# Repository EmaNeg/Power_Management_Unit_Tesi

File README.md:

# Power Management Unit (PMU) per Sistemi Embedded

<div align="center">
  <!-- Sostituisci con i nomi reali dei file immagine esportati -->
  
  &nbsp;&nbsp;&nbsp;&nbsp;&nbsp;&nbsp;&nbsp;&nbsp;&nbsp;&nbsp;&nbsp;&nbsp;&nbsp;&nbsp;&nbsp;&nbsp;&nbsp;&nbsp;
  
</div>

<br>

Questo repository contiene tutti i file di progettazione hardware, le simulazioni e le librerie software per una **Power Management Unit (PMU) integrata**, sviluppata come progetto di Tesi di Laurea Triennale in Ingegneria Elettronica e Tecnologie dell'Informazione presso l'Università degli Studi di Genova.

Il modulo (dimensioni 50x50 mm su PCB a due strati) è progettato per superare il divario tecnologico tra le tensioni variabili delle batterie ai Polimeri di Litio (Li-Po) e le specifiche di alimentazione stabili a 5V richieste dai carichi digitali, garantendo continuità di servizio e sicurezza operativa.

---

## ✨ Caratteristiche Principali (Features)

* **Power Path Management:** Commutazione automatica e trasparente tra sorgente esterna (5V) e batteria, dando priorità all'alimentazione di rete senza azzerare i transitori sul carico.
* **Conversione DC-DC:** Uscita stabile a 5V tramite convertitore Buck-Boost, operante in modo trasparente indipendentemente dallo stato di carica della cella (da 3.0V a 4.2V).
* **Ricarica Li-Po 1S:** Algoritmo CC-CV integrato basato su architettura lineare, con interruzione automatica a 4.2V.
* **Protezione Hardware (BMS):** Modulo di protezione contro sovrascarica (< 2.4V), sovraccarica (> 4.3V) e cortocircuiti.
* **Fuel Gauging I²C:** Stima accurata dello Stato di Carica (SOC) e *alert* hardware tramite algoritmo ModelGauge, senza necessità di resistenze di shunt, azzerando la deriva dell'errore.

---

## 🛠 Architettura Hardware

Il progetto è stato interamente sviluppato utilizzando **KiCad 9.0**. Il sistema si basa sui seguenti circuiti integrati:

| Sottosistema | Modello IC | Produttore | Funzione Principale |
| :--- | :--- | :--- | :--- |
| **DC-DC Converter** | TPS630701 | Texas Instruments | Convertitore Buck-Boost 2.4 MHz fisso a 5V. |
| **Battery Charger** | MCP73831 | Microchip | Controller lineare per ricarica Li-Po 1S (CC-CV). |
| **Fuel Gauge** | MAX17048 | Maxim Integrated | Sensore SOC I²C con algoritmo ModelGauge. |
| **Protection (BMS)** | DW01A + FS8205 | HM Semi / IC Fortune | IC di protezione batteria e doppio MOSFET N-Channel. |
| **Power Path** | DMP1045U-7 | Diodes Inc. | MOSFET P-Channel per commutazione automatica. |

---

## 📊 Prestazioni e Risultati Sperimentali

Il circuito è stato collaudato strumentalmente, registrando ottimi risultati in termini di efficienza energetica e stabilità del segnale:

* **Efficienza Energetica ($\eta$):** Compresa tra il **78.3%** (a pieno carico, ~1.25A) e il **90%** (a carico ridotto, ~100mA).
* **Ripple di Tensione:** Estremamente contenuto, registrando un picco massimo di **60 mV** a 300 mA (90 kHz) e **40 mV** a 1.4 A (390 kHz).
* **Carico Elettrico Massimale:** Il sistema sostiene in sicurezza carichi continui fino a **1.3A a 4.92V** (circa 6.4W in uscita) prima dell'intervento del fusibile resettabile hardware (tarato per sgancio a 1.6A).

<div align="center">
  <!-- Aggiungi nella repo l'immagine dei grafici dell'oscilloscopio se lo desideri -->
  
  &nbsp;&nbsp;&nbsp;&nbsp;&nbsp;&nbsp;
  
</div>

---

## 💻 Libreria Software (Firmware)

A supporto dell'hardware, è stata sviluppata una libreria firmware in **C++** dedicata al sensore MAX17048. 
La libreria permette ai microcontrollori host (es. Arduino, ESP32, STM32) di interfacciarsi facilmente con la PMU per:
- Lettura in tempo reale della tensione della cella ($V_{cell}$) e del SOC (%).
- Monitoraggio del rateo di ricarica/scarica tramite registro `CRATE`.
- Gestione interrupt hardware sul pin `ALRT` per avvisi di sotto-tensione programmabili e sleep mode per il risparmio energetico.

---

## 📁 Struttura della Repository

```text
├── Hardware/
│   ├── Kicad_files/        # File di progetto sorgente (Schematici, Layout PCB)
│   ├── Production/         # File Gerber e Drill pronti per la produzione industriale
│   ├── Assembly/           # File BOM (Bill of Materials) e CPL per assemblaggio SMT Pick & Place
│   └── 3D_Models/          # Rendering 3D della scheda top/bottom (STEP/PNG)
├── Simulations/            # File di simulazione SPICE dei blocchi funzionali (Proteus 8)
├── Firmware/               # Libreria C++ custom per MAX17048 e sketch di test (Arduino)
├── Datasheets/             # PDF dei datasheet originali dei componenti utilizzati
├── Docs/                   # Immagini, grafici di test termici/ripple, schemi e documentazione extra
└── README.md

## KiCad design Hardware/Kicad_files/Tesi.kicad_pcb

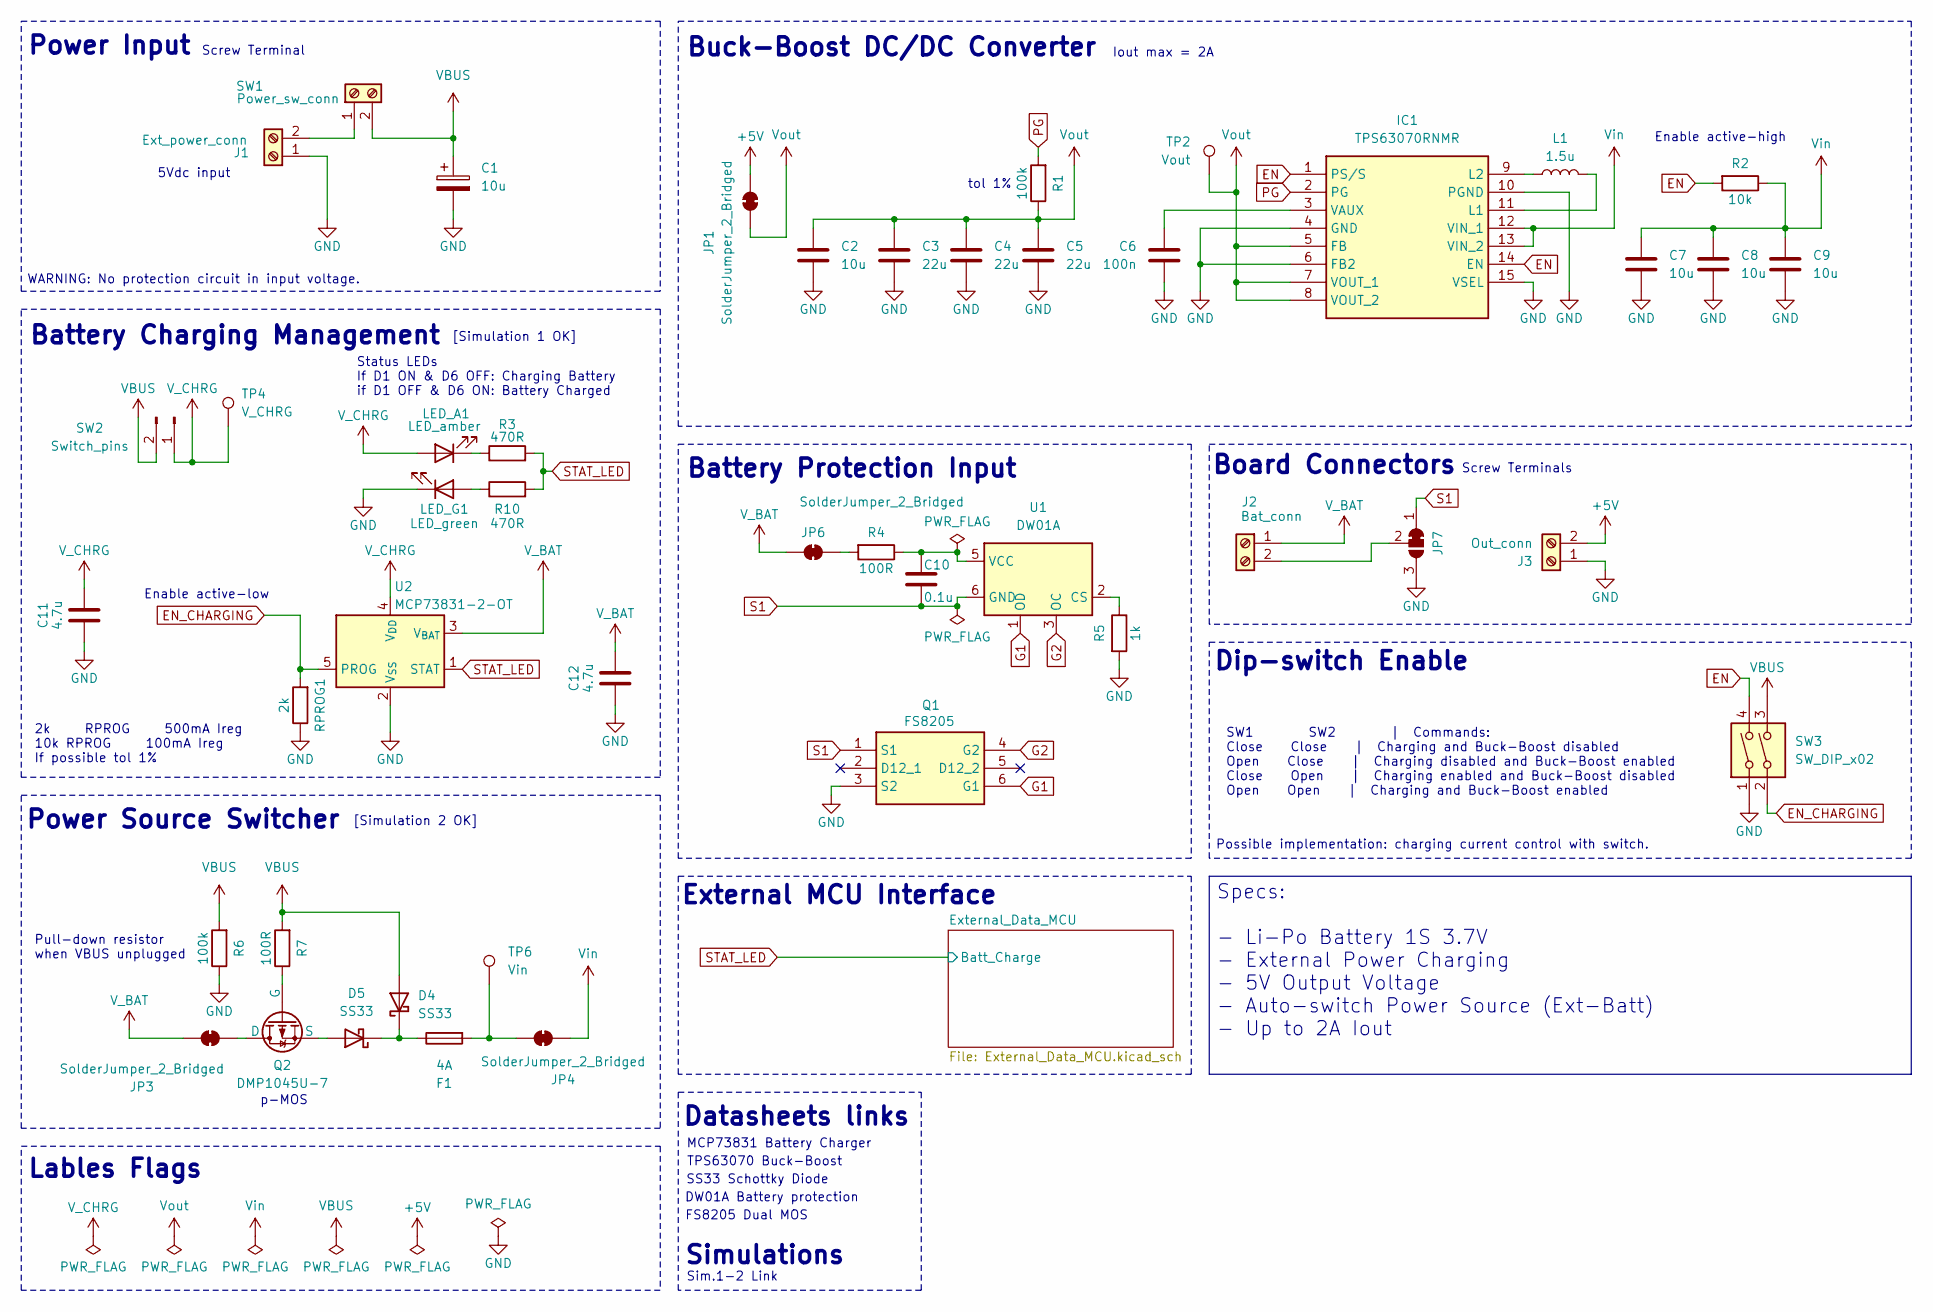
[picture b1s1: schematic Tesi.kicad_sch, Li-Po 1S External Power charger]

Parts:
C1: 10u; CP_EIA-3216-18_Kemet-A
C2, C7: 10u; C_0603_1608Metric
C3, C4, C5: 22u; C_0805_2012Metric
C6: 100n; C_0402_1005Metric
C8, C9: 10u; C_0805_2012Metric
C10: 0.1u; C_0402_1005Metric
C11, C12: 4.7u; C_0603_1608Metric
D4, D5: SS33; D_SMA
F1: 4A; Fuse_1812_4532Metric_Pad1.30x3.40mm_HandSolder
IC1: TPS63070RNMR; TPS630701RNMR; Manufacturer_Part_Number TPS63070RNMR; Mouser Part Number 595-TPS63070RNMR
J1: Ext_power_conn; KF3012P
J2: Bat_conn; KF3012P
J3: Out_conn; KF3012P
JP1, JP3, JP4, JP6: SolderJumper_2_Bridged; SolderJumper-2_P1.3mm_Bridged_RoundedPad1.0x1.5mm
JP7: SolderJumper_3_Bridged12; SolderJumper-3_P1.3mm_Bridged12_RoundedPad1.0x1.5mm_NumberL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
L1: 1.5u; L_Coilcraft_XxL4020
LED_A1: LED_amber; LED_0603_1608Metric
LED_G1: LED_green; LED_0603_1608Metric
Q1: FS8205; Manufacturer_Part_Number FS8205
Q2: DMP1045U-7; SOT-23-GATE
R1: 100k; R_0603_1608Metric
R2: 10k; R_0603_1608Metric
R3, R10: 470R; R_0805_2012Metric
R4, R7: 100R; R_0402_1005Metric
R5: 1k; R_0603_1608Metric
R6: 100k; R_0402_1005Metric
RPROG1: 2k; R_0603_1608Metric
SW1: Power_sw_conn; KF3012P
SW2: Switch_pins; PinHeader_1x02_P2.54mm_Vertical_SMD_Pin1Left
SW3: SW_DIP_x02; SW_DIP_SPSTx02_Slide_KingTek_DSHP02TS_W7.62mm_P1.27mm
TP2: Vout; TestPoint_Pad_D2.0mm
TP4: V_CHRG; TestPoint_Pad_D2.0mm
TP6: Vin; TestPoint_Pad_D2.0mm
U1: DW01A; SOT-23-6
U2: MCP73831-2-OT; SOT-23-5

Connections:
+5V: J3.2, JP1.2 (B)
EN: IC1.1 (PS/S), IC1.14 (EN), R2.2, SW3.4
EN_CHARGING: RPROG1.2, SW3.2, U2.5 (PROG)
G1: Q1.6 (G1), U1.1 (OD)
G2: Q1.4 (G2), U1.3 (OC)
GND: C1.2, C2.2, C3.2, C4.2, C5.2, C6.2, C7.2, C8.2, C9.2, C11.1, C12.1, IC1.4 (GND), IC1.6 (FB2), IC1.10 (PGND), IC1.15 (VSEL), J1.1, J3.1, JP7.3 (B), LED_G1.1 (K), Q1.3 (S2), R5.2, R6.1, RPROG1.1, SW3.1, U2.2 (V_{SS}); also elsewhere on the board
unnamed: D4.1 (K), D5.1 (K), F1.1
unnamed: D5.2 (A), Q2.3 (S)
unnamed: IC1.11 (L1), L1.2
unnamed: IC1.9 (L2), L1.1
unnamed: C6.1, IC1.3 (VAUX)
unnamed: J1.2, SW1.1
unnamed: J2.2, JP7.2 (C)
unnamed: JP3.2 (B), Q2.1 (D)
unnamed: F1.2, JP4.1 (A), TP6.1
unnamed: JP6.2 (B), R4.2
unnamed: LED_A1.1 (K), R3.1
unnamed: LED_G1.2 (A), R10.1
unnamed: Q2.2 (G), R7.1
unnamed: R5.1, U1.2 (CS)
unnamed: C10.2, R4.1, U1.5 (VCC)
PG: IC1.2 (PG), R1.2
S1: C10.1, JP7.1 (A), Q1.1 (S1), U1.6 (GND)
STAT_LED: R3.2, R10.2, U2.1 (STAT); also elsewhere on the board
VBUS: C1.1, D4.2 (A), R6.2, R7.2, SW1.2, SW2.2, SW3.3
V_BAT: C12.2, J2.1, JP3.1 (A), JP6.1 (A), U2.3 (V_{BAT}); also elsewhere on the board
V_CHRG: C11.2, LED_A1.2 (A), SW2.1, TP4.1, U2.4 (V_{DD})
Vin: C7.1, C8.1, C9.1, IC1.12 (VIN_1), IC1.13 (VIN_2), JP4.2 (B), R2.1
Vout: C2.1, C3.1, C4.1, C5.1, IC1.5 (FB), IC1.7 (VOUT_1), IC1.8 (VOUT_2), JP1.1 (A), R1.1, TP2.1

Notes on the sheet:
tol 1%
Power Input
Buck-Boost DC/DC Converter
Lables Flags
Power Source Switcher
Enable active-low
2k RPROG 500mA Ireg 10k RPROG 100mA Ireg If possible tol 1%
Iout max = 2A
Battery Protection Input
[Simulation 2 OK]
Simulations
Enable active-high
MCP73831 Battery Charger
p-MOS
Screw Terminals
External MCU Interface
TPS63070 Buck-Boost
Battery Charging Management
5Vdc input
Datasheets links
FS8205 Dual MOS
[Simulation 1 OK]
DW01A Battery protection
Possible implementation: charging current control with switch.
Board Connectors
SW1 SW2 | Commands: Close Close | Charging and Buck-Boost disabled Open Close | Charging disabled and Buck-Boost enabled Close Open | Charging enabled and Buck-Boost disabled Open Open | Charging and Buck-Boost enabled
SS33 Schottky Diode
WARNING: No protection circuit in input voltage.
Status LEDs If D1 ON & D6 OFF: Charging Battery if D1 OFF & D6 ON: Battery Charged
Dip-switch Enable
Screw Terminal
Pull-down resistor when VBUS unplugged
Sim.1-2 Link
Specs: - Li-Po Battery 1S 3.7V - External Power Charging - 5V Output Voltage - Auto-switch Power Source (Ext-Batt) - Up to 2A Iout

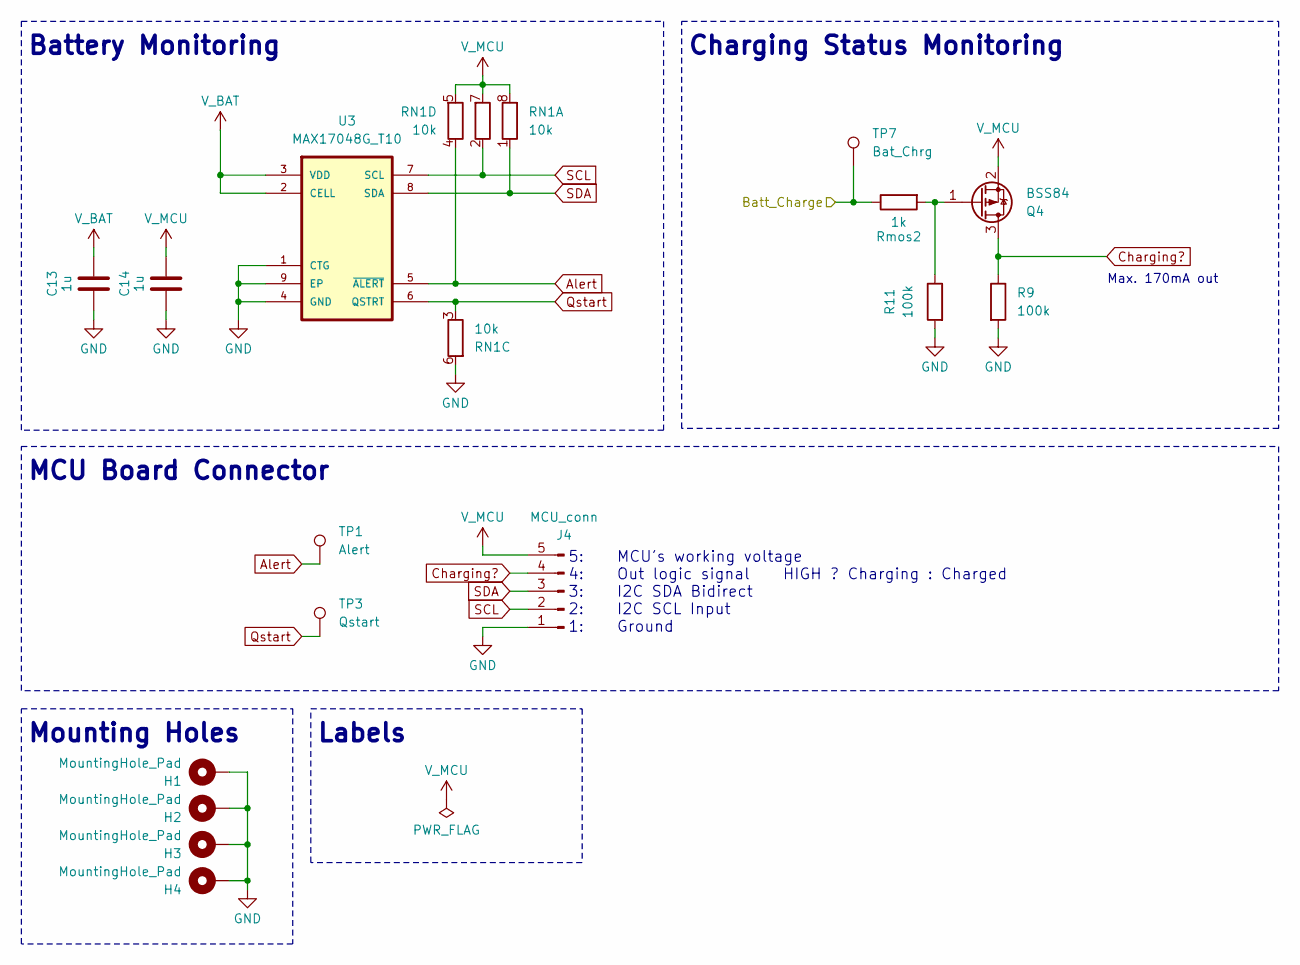
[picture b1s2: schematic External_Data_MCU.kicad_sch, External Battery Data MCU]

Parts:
C13, C14: 1u; C_0603_1608Metric
H1, H2, H3, H4: MountingHole_Pad; MountingHole_2.2mm_M2_DIN965_Pad
J4: MCU_conn; TerminalBlock_Xinya_XY308-2.54-5P_1x05_P2.54mm_Horizontal
Q4: BSS84; SOT-23
R9, R11: 100k; R_0402_1005Metric
RN1: 10k; R_Array_Convex_4x0402
Rmos2: 1k; R_0603_1608Metric
TP1: Alert; Pin_D0.7mm_L6.5mm_W1.8mm_FlatFork
TP3: Qstart; Pin_D0.7mm_L6.5mm_W1.8mm_FlatFork
TP7: Bat_Chrg; TestPoint_Pad_D2.0mm
U3: MAX17048G_T10; SON50P200X200X80-9N

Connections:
Alert: RN1.4 (R4.1), TP1.1, U3.5 (~ALERT)
Charging?: J4.4, Q4.3 (D), R9.1
GND: C13.1, C14.1, H1.1, H2.1, H3.1, H4.1, J4.1, R9.2, R11.2, RN1.6 (R3.2), U3.1 (CTG), U3.4 (GND), U3.9 (EP); also elsewhere on the board
unnamed: Q4.1 (G), R11.1, Rmos2.2
Qstart: RN1.3 (R3.1), TP3.1, U3.6 (QSTRT)
SCL: J4.2, RN1.2 (R2.1), U3.7 (SCL)
SDA: J4.3, RN1.1 (R1.1), U3.8 (SDA)
STAT_LED: Rmos2.1, TP7.1; also elsewhere on the board
V_BAT: C13.2, U3.2 (CELL), U3.3 (VDD); also elsewhere on the board
V_MCU: C14.2, J4.5, Q4.2 (S), RN1.5 (R4.2), RN1.7 (R2.2), RN1.8 (R1.2)

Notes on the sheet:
Max. 170mA out
Mounting Holes
MCU Board Connector
Labels
Battery Monitoring
Charging Status Monitoring
5: MCU's working voltage 4: Out logic signal HIGH ? Charging : Charged 3: I2C SDA Bidirect 2: I2C SCL Input 1: Ground

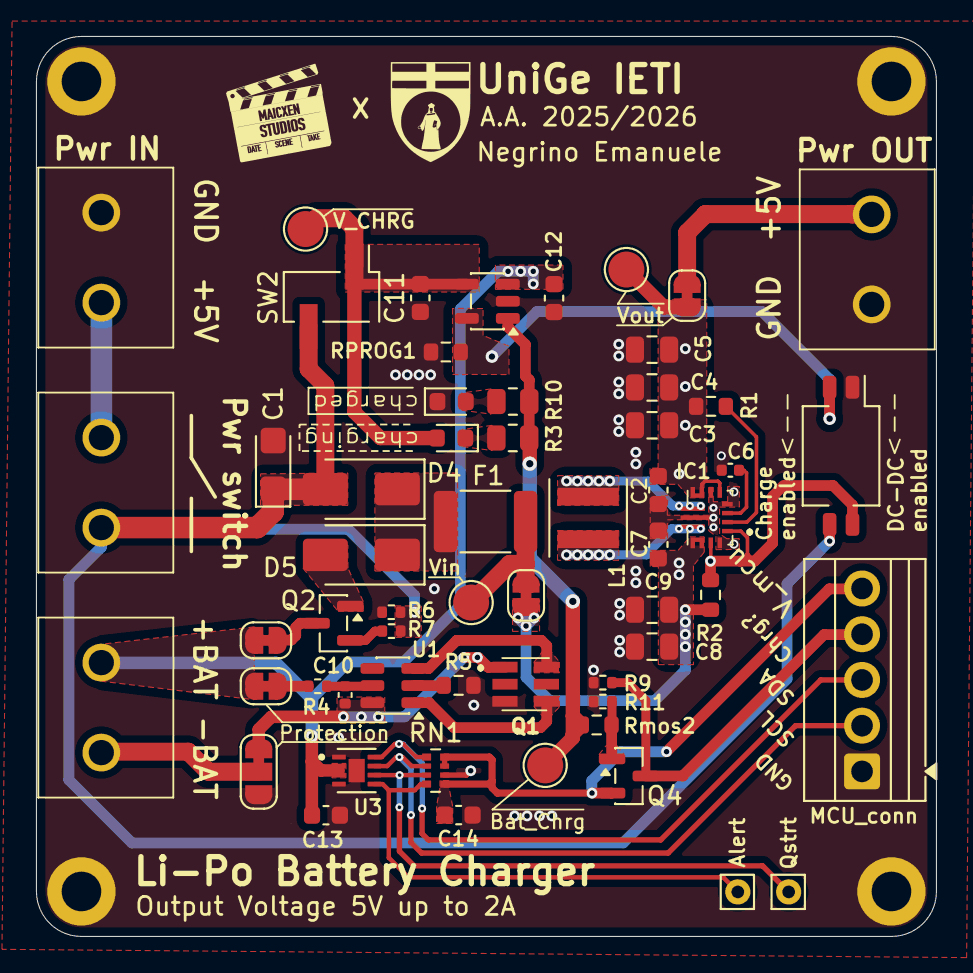
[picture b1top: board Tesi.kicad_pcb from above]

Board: 2 copper layers, 50.0 x 50.0 mm, 62 parts (0 on the bottom side), 36 nets.

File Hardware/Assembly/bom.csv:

Designator,Footprint,Quantity,Value,LCSC Part #
C1,CP_EIA-3216-18_Kemet-A,1,10u,
C10,0402,1,0.1u,
"C11, C12",0603,2,4.7u,
"C13, C14",0603,2,1u,
"C2, C7",0603,2,10u,
"C3, C4, C5",0805,3,22u,
C6,0402,1,100n,
"C8, C9",0805,2,10u,
"D4, D5",D_SMA,2,SS33,
F1,1812,1,4A,
IC1,TPS630701RNMR,1,TPS63070RNMR,
J1,KF3012P,1,Ext_power_conn,
J2,KF3012P,1,Bat_conn,
J3,KF3012P,1,Out_conn,
J4,TerminalBlock_Xinya_XY308-2.54-5P_1x05_P2.54mm_Horizontal,1,MCU_conn,
L1,L_Coilcraft_XxL4020,1,1.5u,
LED_A1,0603,1,LED_amber,
LED_G1,0603,1,LED_green,
Q1,FS8205,1,FS8205,
Q2,SOT-23-GATE,1,DMP1045U-7,
Q4,SOT-23,1,BSS84,
R1,0603,1,100k,
"R10, R3",0805,2,470R,
"R11, R6, R9",0402,3,100k,
R2,0603,1,10k,
"R4, R7",0402,2,100R,
"R5, RMOS2",0603,2,1k,
RN1,R_Array_Convex_4x0402,1,10k,
RPROG1,0603,1,2k,
SW1,KF3012P,1,Power_sw_conn,
SW2,PinHeader_1x02_P2.54mm_Vertical_SMD_Pin1Left,1,Switch_pins,
SW3,SW_DIP_SPSTx02_Slide_KingTek_DSHP02TS_W7.62mm_P1.27mm,1,SW_DIP_x02,
TP1,Pin_D0.7mm_L6.5mm_W1.8mm_FlatFork,1,Alert,
TP2,TestPoint_Pad_D2.0mm,1,Vout,
TP3,Pin_D0.7mm_L6.5mm_W1.8mm_FlatFork,1,Qstart,
TP4,TestPoint_Pad_D2.0mm,1,V_CHRG,
TP6,TestPoint_Pad_D2.0mm,1,Vin,
TP7,TestPoint_Pad_D2.0mm,1,Bat_Chrg,
U1,SOT-23-6,1,DW01A,
U2,SOT-23-5,1,MCP73831-2-OT,
U3,SON50P200X200X80-9N,1,MAX17048G_T10,

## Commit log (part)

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2026-05-03 Added kicad files
2026-06-01 Changed names
2026-06-01 added folders
2026-06-01 sim added
2026-06-02 added docs
2026-06-02 added image
2026-06-02 added 3d
2026-06-02 added pdf
2026-06-20 added .wrl

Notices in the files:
README.md:
License: MIT
